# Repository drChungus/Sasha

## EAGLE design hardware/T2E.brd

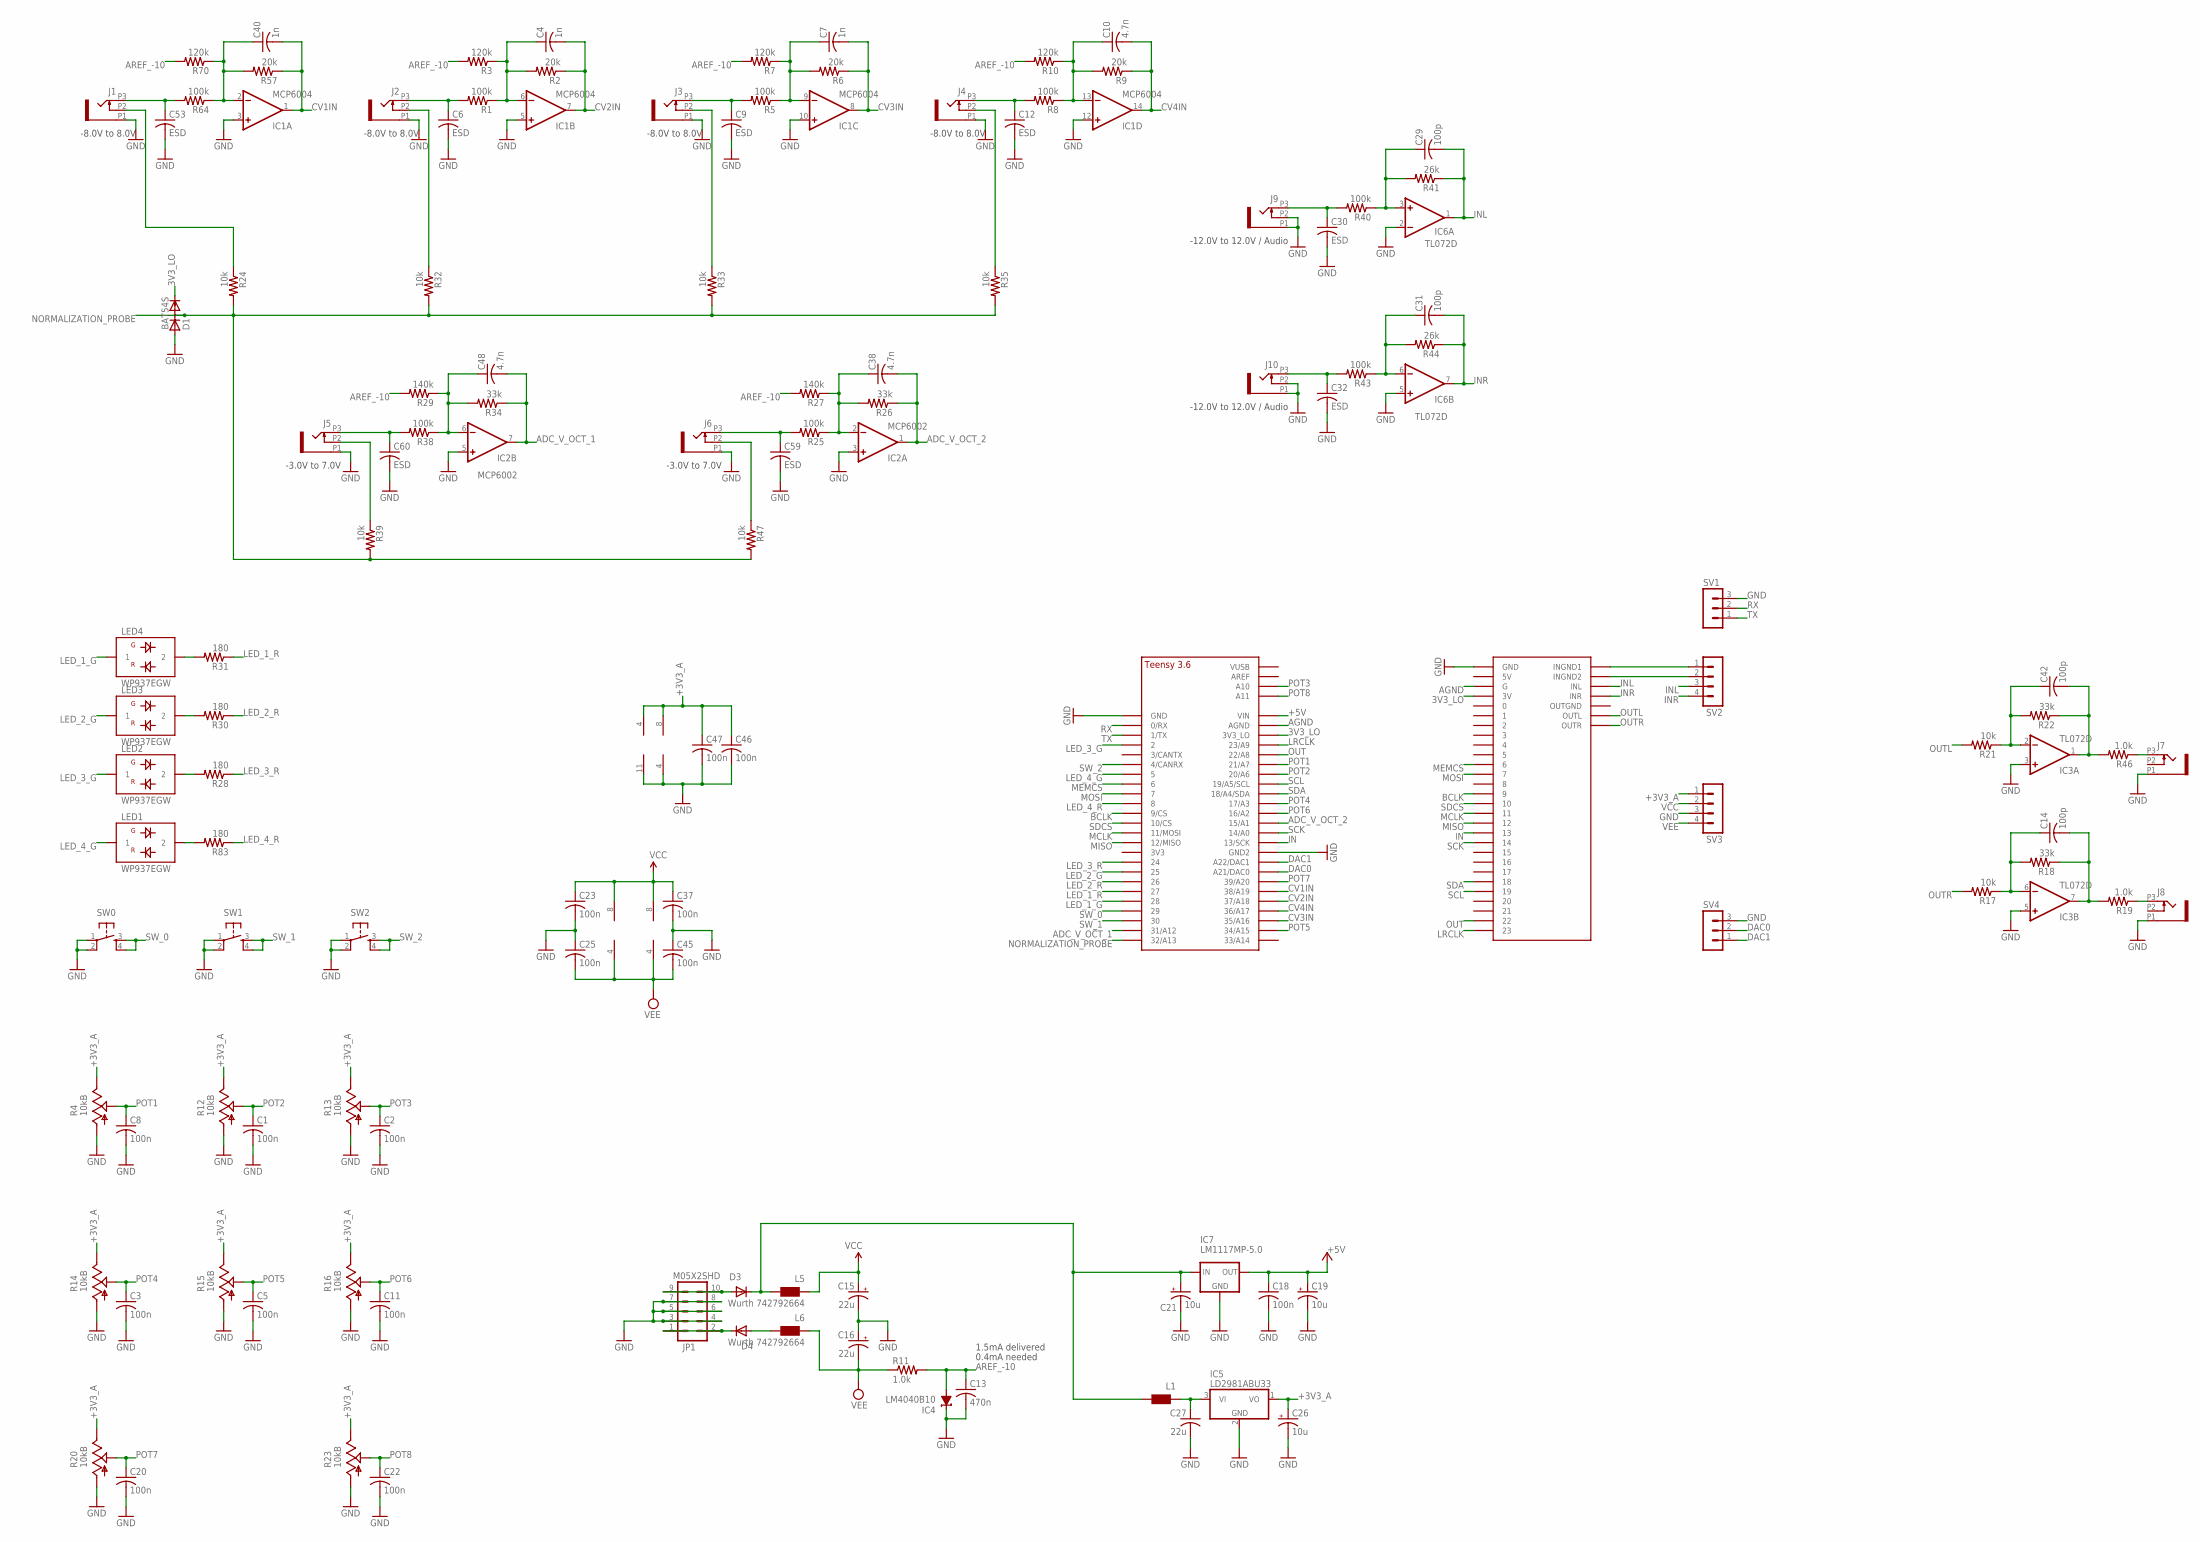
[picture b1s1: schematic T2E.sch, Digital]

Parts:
C1, C2, C3, C5, C8, C11, C18, C20, C22, C23, C25, C37, C45, C46, C47: 100n; C0603
C4, C7, C40: 1n; C0603
C6, C9, C12, C30, C32, C53, C59, C60: ESD; C0603
C10, C38, C48: 4.7n; C0603
C13: 470n; C0603
C14, C29, C31, C42: 100p; C0603
C15, C16: 22u; PANASONIC_C
C19, C21: 10u; PANASONIC_C
C26: 10u; PANASONIC_A
C27: 22u; C1206
D1: BAT54S; SOT23
D3, D4: 1N5819HW; SOD123
IC1: MCP6004; SO14
IC2: MCP6002; SO08
IC3, IC6: TL072D; SO08
IC4: LM4040B10; DBZ_R-PDSO-G3
IC5: LD2981ABU33; SOT89
IC7: LM1117MP-5.0; SOT223
J1, J2, J3, J4, J5, J6, J7, J8, J9, J10: PJ301_THONKICONN6; WQP_PJ_301M6
JP1: M05X2SHD; 2X5-SHROUDED
L1: WE-CBF_0603; 0603
L5, L6: Wurth 742792664; 0603
LED1, LED2, LED3, LED4: WP937EGW; LED3MM
R1, R5, R8, R25, R38, R40, R43, R64: 100k; R0603
R2, R6, R9, R57: 20k; R0603
R3, R7, R10, R70: 120k; R0603
R4, R12, R13, R14, R15, R16, R20, R23: 10kB; ALPS_POT_VERTICAL_PS
R11, R19, R46: 1.0k; R0603
R17, R21, R24, R32, R33, R35, R39, R47: 10k; R0603
R18, R22, R26, R34: 33k; R0603
R27, R29: 140k; R0603
R28, R30, R31, R83: 180; R0603
R41, R44: 26k; R0603
SV1, SV4: MA03-1
SV2, SV3: MA04-1
SW0, SW1, SW2: TAC_SWITCHPTH; TACTILE-PTH
U$1: TeensyAudioShield Rev C.; AUDIOSHIELD
U$4: TEENSY_3.5/3.6_BASIC

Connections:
3V3_LO: D1.2 (C), U$1.3V, U$4.3V3_LO
+3V3_A: C26.+, C46.1, C47.1, IC1.4 (V+), IC2.8 (V+), IC5.1 (VO), R4.P$1 (E), R12.P$1 (E), R13.P$1 (E), R14.P$1 (E), R15.P$1 (E), R16.P$1 (E), R20.P$1 (E), R23.P$1 (E), SV3.1
+5V: C18.1, C19.+, IC7.2 (OUT), IC7.4 (OUT), U$4.VIN
ADC_V_OCT_1: C48.2, IC2.7 (OUT), R34.1, U$4.31/A12
ADC_V_OCT_2: C38.2, IC2.1 (OUT), R26.1, U$4.15/A1
AGND: U$1.G, U$4.AGND
AREF_-10: C13.1, IC4.2 (A), R3.2, R7.2, R10.2, R11.2, R27.2, R29.2, R70.2
BCLK: U$1.9, U$4.9/CS
CV1IN: C40.2, IC1.1 (OUT), R57.1, U$4.38/A19
CV2IN: C4.2, IC1.7 (OUT), R2.1, U$4.37/A18
CV3IN: C7.2, IC1.8 (OUT), R6.1, U$4.35/A16
CV4IN: C10.2, IC1.14 (OUT), R9.1, U$4.36/A17
DAC0: SV4.2, U$4.21/DAC0 (A21/DAC0)
DAC1: SV4.1, U$4.A22/DAC1
GATE_IN1: C59.1, J6.P3 (3), R25.2
GND: C1.2, C2.2, C3.2, C5.2, C6.2, C8.2, C9.2, C11.2, C12.2, C13.2, C15.-, C16.+, C18.2, C19.-, C20.2, C21.-, C22.2, C23.2, C25.1, C26.-, C27.2, C30.2, C32.2, C37.2, C45.1, C46.2, C47.2, C53.2, C59.2, C60.2, D1.1 (A), IC1.3 (+IN), IC1.5 (+IN), IC1.10 (+IN), IC1.11 (V-), IC1.12 (+IN), IC2.3 (+IN), IC2.4 (V-), IC2.5 (+IN), IC3.3 (+IN), IC3.5 (+IN), IC4.1 (C), IC5.2 (GND), IC6.2 (-IN), IC6.5 (+IN), IC7.1 (GND), J1.P1 (1), J2.P1 (1), J3.P1 (1), J4.P1 (1), J5.P1 (1), J6.P1 (1), J7.P1 (1), J8.P1 (1), J9.P1 (1), J9.P2 (2), J10.P1 (1), J10.P2 (2), JP1.3, JP1.4, JP1.5, JP1.6, JP1.7, JP1.8, R4.P$3 (A), R12.P$3 (A), R13.P$3 (A), R14.P$3 (A), R15.P$3 (A), R16.P$3 (A), R20.P$3 (A), R23.P$3 (A), SV1.3, SV3.3, SV4.3, SW0.1, SW0.2, SW1.1, SW1.2, SW2.1, SW2.2, U$1.GND, U$4.GND, U$4.GND2
IN: U$1.13, U$4.13/SCK
INL: C29.2, IC6.1 (OUT), R41.1, SV2.3, U$1.INL
INR: C31.2, IC6.7 (OUT), R44.1, SV2.4, U$1.INR
LED_1_G: LED4.1, U$4.28
LED_1_R: R31.1, U$4.27
LED_2_G: LED3.1, U$4.25
LED_2_R: R30.1, U$4.26
LED_3_G: LED2.1, U$4.2
LED_3_R: R28.1, U$4.24
LED_4_G: LED1.1, U$4.5
LED_4_R: R83.1, U$4.8
LRCLK: U$1.23, U$4.23/A9
MCLK: U$1.11, U$4.11/MOSI
MEMCS: U$1.6, U$4.6
MISO: U$1.12, U$4.12/MISO
MORPH_IN: C53.1, J1.P3 (3), R64.2
MORPH_IN1: C6.1, J2.P3 (3), R1.2
MORPH_IN2: C9.1, J3.P3 (3), R5.2
MORPH_IN3: C12.1, J4.P3 (3), R8.2
MORPH_IN4: C30.1, J9.P3 (3), R40.2
MORPH_IN5: C32.1, J10.P3 (3), R43.2
MOSI: U$1.7, U$4.7
unnamed: C4.1, IC1.6 (-IN), R1.1, R2.2, R3.1
unnamed: C7.1, IC1.9 (-IN), R5.1, R6.2, R7.1
unnamed: C10.1, IC1.13 (-IN), R8.1, R9.2, R10.1
unnamed: C14.1, IC3.6 (-IN), R17.1, R18.2
unnamed: D3.A, JP1.9, JP1.10
unnamed: C14.2, IC3.7 (OUT), R18.1, R19.2
unnamed: D4.C, JP1.1, JP1.2
unnamed: J8.P3 (3), R19.1
unnamed: SV2.1, U$1.INGND1
unnamed: C40.1, IC1.2 (-IN), R57.2, R64.1, R70.1
unnamed: D4.A, L6.2
unnamed: C38.1, IC2.2 (-IN), R25.1, R26.2, R27.1
unnamed: SV2.2, U$1.INGND2
unnamed: C29.1, IC6.3 (+IN), R40.1, R41.2
unnamed: LED2.2, R28.2
unnamed: J5.P2 (2), R39.1
unnamed: LED3.2, R30.2
unnamed: LED4.2, R31.2
unnamed: C31.1, IC6.6 (-IN), R43.1, R44.2
unnamed: J3.P2 (2), R33.1
unnamed: J2.P2 (2), R32.1
unnamed: J1.P2 (2), R24.1
unnamed: J4.P2 (2), R35.1
unnamed: C48.1, IC2.6 (-IN), R29.1, R34.2, R38.1
unnamed: J6.P2 (2), R47.1
unnamed: C21.+, D3.C, IC7.3 (IN), L1.2, L5.2
unnamed: C27.1, IC5.3 (VI), L1.1
unnamed: LED1.2, R83.2
unnamed: C42.1, IC3.2 (-IN), R21.1, R22.2
unnamed: C42.2, IC3.1 (OUT), R22.1, R46.2
unnamed: J7.P3 (3), R46.1
NORMALIZATION_PROBE: D1.3 (AC), R24.2, R32.2, R33.2, R35.2, R39.2, R47.2, U$4.32/A13
OUT: U$1.22, U$4.22/A8
OUTL: R21.2, U$1.OUTL
OUTR: R17.2, U$1.OUTR
POT1: C8.1, R4.P$2 (S), U$4.21/A7
POT2: C1.1, R12.P$2 (S), U$4.20/A6
POT3: C2.1, R13.P$2 (S), U$4.A10
POT4: C3.1, R14.P$2 (S), U$4.17/A3
POT5: C5.1, R15.P$2 (S), U$4.34/A15
POT6: C11.1, R16.P$2 (S), U$4.16/A2
POT7: C20.1, R20.P$2 (S), U$4.39/A20
POT8: C22.1, R23.P$2 (S), U$4.A11
RX: SV1.2, U$4.0/RX
SCK: U$1.14, U$4.14/A0
SCL: U$1.19, U$4.19/A5/SCL
SDA: U$1.18, U$4.18/A4/SDA
SDCS: U$1.10, U$4.10/CS
SW_0: SW0.3, SW0.4, U$4.29
SW_1: SW1.3, SW1.4, U$4.30
SW_2: SW2.3, SW2.4, U$4.4/CANRX
TX: SV1.1, U$4.1/TX
VCC: C15.+, C23.1, C37.1, IC3.8 (V+), IC6.8 (V+), L5.1, SV3.2
VEE: C16.-, C25.2, C45.2, IC3.4 (V-), IC6.4 (V-), L6.1, R11.1, SV3.4
V_OCT_IN: C60.1, J5.P3 (3), R38.2

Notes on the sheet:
-8.0V to 8.0V
0.4mA needed
1.5mA delivered
-3.0V to 7.0V
-12.0V to 12.0V / Audio

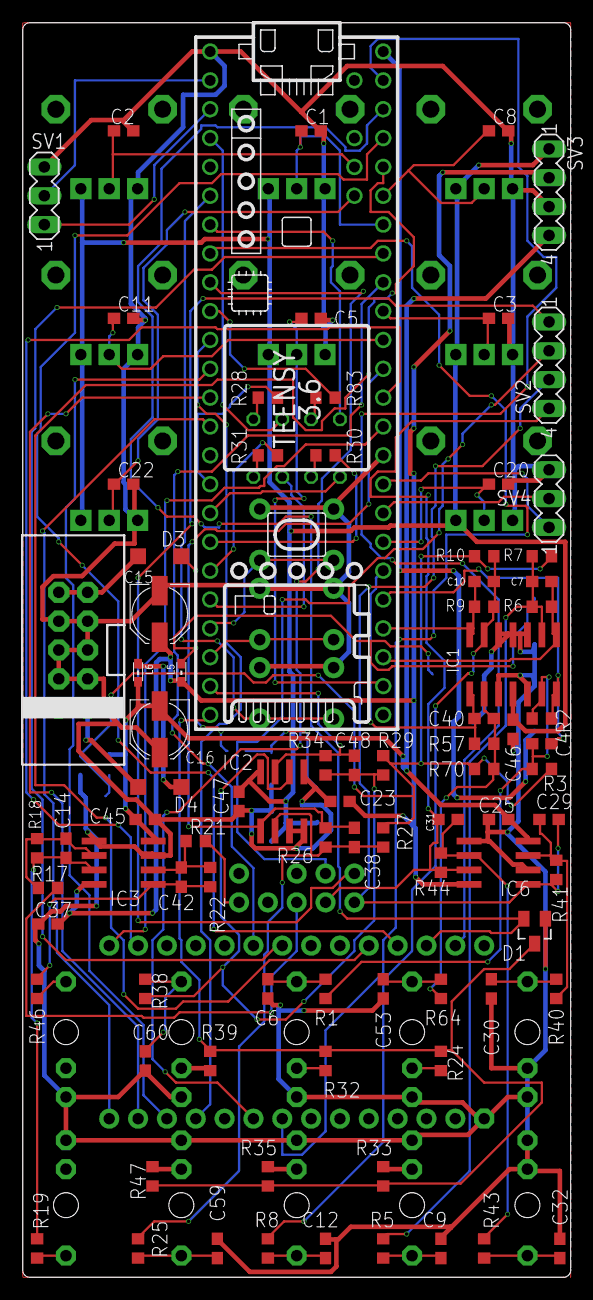
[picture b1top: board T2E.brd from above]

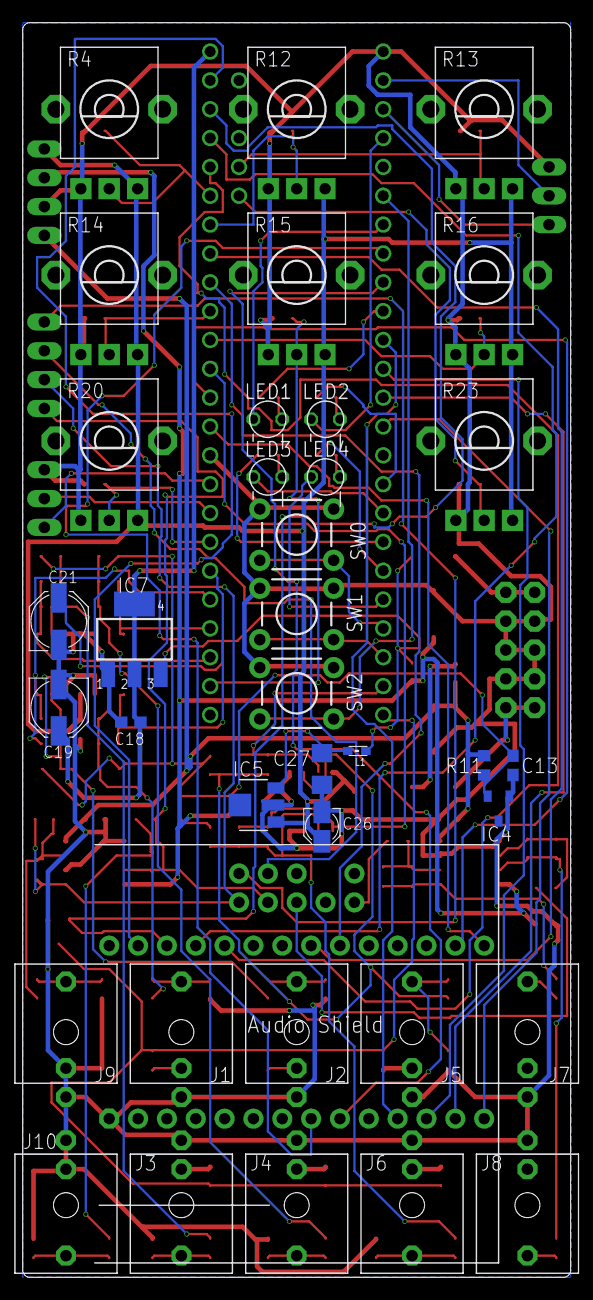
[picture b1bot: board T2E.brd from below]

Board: 2 copper layers, 48.3 x 110.5 mm, 125 parts (37 on the bottom side), 93 nets.

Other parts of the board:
U$3: EURO_PCB_10HP

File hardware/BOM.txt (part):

Partlist exported from C:/Users/tvirag/Dropbox/Projektek/teensyEurorackBoard/T2E.sch at 2021. 02. 11. 16:52

Part Value                                                                Device                                                               Package                            Description                                  CIIVA_IDS CODE__JEDEC COMPONENT_LINK_1_DESCRIPTION COMPONENT_LINK_1_URL                COMPONENT_LINK_3_DESCRIPTION COMPONENT_LINK_3_URL                                                          COMPONENT_LINK_4_DESCRIPTION COMPONENT_LINK_4_URL                                           DATASHEET                                                          DATASHEET_VERSION FOOTPRINT_VARIANT_NAME_0 FOOTPRINT_VARIANT_NAME_1 FOOTPRINT_VARIANT_NAME_2 IMPORTED IMPORTED_FROM IMPORT_TS  IOUT_MAX MF                MOUNTING_TECHNOLOGY MPN               OC_FARNELL OC_NEWARK PACKAGE PACKAGE_DESCRIPTION                                                           PACKAGE_VERSION   PACKING POPULARITY PREFIX PRESET_VOUT_VALUES_V RELEASE_DATE SUPPLY_CURRENT_IGND__SMALL_LOAD VAULT_GUID                           VAULT_REVISION                       VIN_MAX_V VIN_MIN_V
C1   100n                                                                 C-USC0603                                                            C0603                              CAPACITOR, American symbol                                                                                                                                                                                                                                                                                                                                                                                                                                                                                                                                                                                                                                                                                                                                                                                                                                                                                                          
C2   100n                                                                 C-USC0603                                                            C0603                              CAPACITOR, American symbol                                                                                                                                                                                                                                                                                                                                                                                                                                                                                                                                                                                                                                                                                                                                                                                                                                                                                                          
C3   100n                                                                 C-USC0603                                                            C0603                              CAPACITOR, American symbol                                                                                                                                                                                                                                                                                                                                                                                                                                                                                                                                                                                                                                                                                                                                                                                                                                                                                                          
C4   1n                                                                   C-USC0603                                                            C0603                              CAPACITOR, American symbol                                                                                                                                                                                                                                                                                                                                                                                                                                                                                                                                                                                                                                                                                                                                                                                                                                                                                                          
C5   100n                                                                 C-USC0603                                                            C0603                              CAPACITOR, American symbol                                                                                                                                                                                                                                                                                                                                                                                                                                                                                                                                                                                                                                                                                                                                                                                                                                                                                                          
C6   ESD                                                                  C-USC0603                                                            C0603                              CAPACITOR, American symbol                                                                                                                                                                                                                                                                                                                                                                                                                                                                                                                                                                                                                                                                                                                                                                                                                                                                                                          
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
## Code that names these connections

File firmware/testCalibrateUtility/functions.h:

frontPanel currentFrontPanel, previousFrontPanel;
struct frontPanel myFrontPanels[6];
int frontPanelPage;

frontPanel readFrontPanel(){
  frontPanel currentFrontPanel;
  currentFrontPanel.pot1 = map(analogRead(pot1pin),0,4095,0,255);
  currentFrontPanel.pot2 = map(analogRead(pot2pin),0,4095,0,255);
  currentFrontPanel.pot3 = map(analogRead(pot3pin),0,4095,0,255);
  currentFrontPanel.pot4 = map(analogRead(pot4pin),0,4095,0,255);
  currentFrontPanel.pot5 = map(analogRead(pot5pin),0,4095,0,255);
  currentFrontPanel.pot6 = map(analogRead(pot6pin),0,4095,0,255);
  currentFrontPanel.pot7 = map(analogRead(pot7pin),0,4095,0,255);
  currentFrontPanel.pot8 = map(analogRead(pot8pin),0,4095,0,255);
  currentFrontPanel.button1 = !digitalRead(button1pin);
  currentFrontPanel.button2 = !digitalRead(button2pin);
  currentFrontPanel.button3 = !digitalRead(button3pin);
  return currentFrontPanel;
};


int searchStructDiffIndex (frontPanel s1, frontPanel s2){
    int diffIndex = -1;
    for (int i = 0; i < 9; ++i) //check Pots /////1 only!!!
    {
      if( abs(s1[i] - s2[i]) > potTolerance){
        diffIndex = i; //this indexin works, but it is shady AF
      };
    }    
    for (int i = 1; i < 4; ++i) //CheckButtons
    {
      if(s1(i*10) != s2(i*10)){
        diffIndex = frontPanelIndexCatalog[i+7];
      };
    }
    return diffIndex;
};

int showStructValue (frontPanel thisPanel, int diffIndex){
  int Value;
  if (diffIndex < 10){
    Value = thisPanel[diffIndex];
  }
  else {
    Value= thisPanel(diffIndex);
  }
  return Value;
};

void updateLEDs(byte colorCode){
  led4.setColor(colorCode & 0b11);    //led colors encoded in one byte, MSB to LSB order
  led3.setColor((colorCode & 0b1100)>>2);
  led2.setColor((colorCode & 0b110000)>>4);
  led1.setColor((colorCode & 0b11000000)>>6);
  led1.drive();
  led2.drive();
  led3.drive();
  led4.drive();
}
double readCV(int pin){
  double sum;
  for (int i=0; i<10; i++){ ///use 10000 samples for calibration and do every voltage! It makes sense to check the voltage source with a high precision meter, as the reference can also be off!
    sum+=analogRead(pin);
  }
  double dataValue = sum/10;
  dataValue = (dataValue-3149.1) / -409;
;
  return dataValue;  
}

int getBit(int code, int posi){ //LSB based
  int masked= ( code & (0b01<<posi) ) >> posi;
  return masked;
}

void fpEventHandler(){
  currentFrontPanel = readFrontPanel();
  int diffIndex = searchStructDiffIndex(previousFrontPanel, currentFrontPanel);  
  if (diffIndex != -1){
    int newValue = showStructValue(currentFrontPanel, diffIndex);
    Serial.print("Difference at index ");Serial.print(diffIndex);
    Serial.print(" New value: ");Serial.println(newValue);
    if ((currentFrontPanel.button3 > previousFrontPanel.button3) && (frontPanelPage < 4))
    {
      frontPanelPage++;
    }
    if ((currentFrontPanel.button1 > previousFrontPanel.button1) && (frontPanelPage > 0))
    {
      frontPanelPage--;
    }
    Serial.println(frontPanelPage); 
    updateLEDs(fpLedLut[frontPanelPage]);
    if (diffIndex < 10)
    {
      myFrontPanels[frontPanelPage][diffIndex] = currentFrontPanel[diffIndex];
    }
    
    previousFrontPanel = currentFrontPanel;
  }
}
double scaleSimple(double x, double in_min, double in_max, double out_min, double out_max)
{
  double limitedOut;
  limitedOut = (x - in_min) * (out_max - out_min) / (in_max - in_min) + out_min;
  return limitedOut;
}

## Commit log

2021-06-10 Github Migration
    Migrated project from Dropbox to GitHub for firmware development
2021-06-10 FrontPanel event detection Draft
    draft only
2021-06-10 FP Update Works
    fron panel struct update event generator tested and works
2021-06-10 Added LED colors
2021-06-10 Started Calibration
    Started Calibration calc
2021-06-10 Completed Calibration algorithm
    It works like a charm!
2021-06-11 Added Audio Design
    draft state currently
2021-06-11 Redone Audio Design
2021-06-11 Audo Engine handling
2021-06-11 FP update
    Added Scale function and multiple virtual Front Panels, plus stepping between them.
2021-06-11 Update functions.h
    fixed struct array definition
2021-06-13 PAge sys update
2021-06-13 Algorithm LUT implementation
    algorith dependent connections can be made, with LSB = MIXR ch4 codes
2021-06-13 Pots Update
    Amplitude Control put to pots directly
2021-06-14 Forked Operator
    Added main Pitch knob
2021-06-14 Added level CV
2021-06-16 Numerous updates on UI
    Changed page behavior, preparations for waveform selection
2021-06-16 Added waveform generator and waveform data
    Waveforms based on OP3
2021-06-16 Testing and Bug Fixes
2021-06-17 New Algo LED animation and implemented waveform selection
2021-06-17 Fixed type cast issues
2021-06-17 Fixed pointer isues
2021-06-17 testing Waveform selector
    it does not work with my own waveforms :(
2021-06-18 fine tuning
2021-06-19 Added Waveform selection
    And CV for all basic OP parameters
2021-06-19 Added EEPROM
    and there uis something wrong with the engine
2021-06-19 Revert "Added EEPROM"
    This reverts commit a0affef21f0e1a02f36fd4da3cec7c0edcaade0d.
2021-06-19 Revert "Revert "Added EEPROM""
    This reverts commit 28e034bdabe43a6bc8a0b5e3649a4749fc5d8d1d.
2021-06-19 added EEPROM panel load
    works but only almost
2021-06-24 Added Chords FW
2021-06-25 Ported old code to new framework
2021-07-05 Update Satsuire.ino
    Functionality Verified on HW
2021-07-12 Addeed framework for Vocoder project
2021-07-14 Created Simple Branh
    Sachi Light it is. For pot to function simoplified FM (PM ) voice
2021-07-25 Update audioLibraryDesign.h
    Added Filter Envelope
2021-07-25 Implemented econd light architecture
    External Triggering and Normalization tetection to be done
2021-07-25 Started Trigger Detection
2021-07-26 Added External Trigger
    Next up: CV controls
2021-07-28 Tweakz
2021-07-31 Added Waveshaper array generation, and found some bugs
2021-07-31 Revert "Added Waveshaper array generation, and found some bugs"
    This reverts commit ab0c73b564c2920f0b9aa3d607075353e252b9f8.
2021-07-31 Revert "Tweakz"
    This reverts commit 84efd2fb4d27a35fd9aa1f98426aa41ff302ceb6.
2021-07-31 Revert "Update audioEngine.ino"
    This reverts commit 33d9b9761b5fb354f1118bdce154b4ac04c47892.
2021-07-31 Fixes
2021-07-31 FIXED, Waveshaper Init is bad
2021-07-31 Added Waveshaper
    And fixed all them bugs
2022-01-31 Ladder Filter Initial Commit
    PoC done, L in is fucked, resonance becomes unstable if controlled by pot
2022-02-07 Added Ladder FW
    FB res for analog ins ashall be 220p

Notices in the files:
parts and their libraries:
lm1117: (c) 2014 Samuel Lourenço
